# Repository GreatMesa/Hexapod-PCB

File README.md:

# Hexapod-PCB
### 4-Layer PCB for the Arduino Hexapod

## Introduction
This PCB is a 4-Layer hexapod for servo applications. It containes a signal layer for all the servo pwm pins and a uniform ground + power plane for the servos spesifically. The reason while I decided to go through this project is because I wanted a way that I can adjust the voltage level of the servos as depending on the voltage of the servos the speed and tourque is affected. This also will organize my wire managment by a lot since I don't have to extrapolate my electonics to a bunch of breadboards.

## Goals
Here are the main goals of this PCB:
- Make a PCB that can manage 18 seperate servos simutaneously.
- Have uniform and stable power for all 18 servos.
- Make calculations using a inertial sensor for inverse kinematics.
- Use NRF protocol to communicate with a RC transmitter.
- Have indication for the hexapod status using LEDs and a Buzzer.
## PCB 3D Model

## PCB Picture

## Bill of Materials
| Item Name                | Price (USD) | Quantity | Total Price (USD) | Purchase Link                                                                                                                                                                                                                                                                                                                                                                                                                                                                                                                                                                                                                                                                                 |
|--------------------------|-------------|----------|--------------------|----------------------------------------------------------------------------------------------------------------------------------------------------------------------------------------------------------------------------------------------------------------------------------------------------------------------------------------------------------------------------------------------------------------------------------------------------------------------------------------------------------------------------------------------------------------------------------------------------------------------------------------------------------------------------------------------|
| PCB Order               | $33.15      | 1        | $33.15             | [Link](https://www.pcbway.com/QuickOrderOnline.aspx)                                                                                                                                                                                                                                                                                                                                                                                                                                                                                                                                                                                                                                            |
| Teensy 4.1              | $37.50      | 1        | $37.50             | [Link](https://www.amazon.com/PJRC-Cortex-M7-Processor-iMXRT1062-Without/dp/B088JY7P2H)                                                                                                                                                                                                                                                                                                                                                                                                                                                                                                                                                                                                         |
| Male Pin Header Strips  | OWNED       | OWNED    | OWNED              | [Link](https://www.amazon.com/Straight-Breakaway-Connector-Breadboard-Electronic/dp/B09MYBRW3F)                                                                                                                                                                                                                                                                                                                                                                                                                                                                                                                                                                                                |
| Female Pin Header Strips| $0.99       | 1        | $0.99              | [Link](https://www.aliexpress.us/item/2251832850099221.html)                                                                                                                                                                                                                                                                                                                                                                                                                                                                                                                                                                                                                                   |
| 7.4 5200mAh Lipo        | $15.97      | 1        | $15.97             | [Link](https://www.amazon.com/Zeee-5200mAh-Battery-Truggy-Airplane/dp/B06ZYRCPS3)                                                                                                                                                                                                                                                                                                                                                                                                                                                                                                                                                                                                               |
| ACS712 Current Sensor   | $1.15       | 1        | $1.15              | [Link](https://lcsc.com/product-detail/Current-Sensors_ALLEGRO-ACS712ELCTR-05B-T_C44471.html)                                                                                                                                                                                                                                                                                                                                                                                                                                                                                                                                                                                                  |
| WS2812B Individual LEDs | $0.41       | 1        | $0.41              | [Link](https://lcsc.com/product-detail/RGB-LEDs-Built-in-IC_XINGLIGHT-XL-5050RGBC-WS2812B_C2843785.html)                                                                                                                                                                                                                                                                                                                                                                                                                                                                                                                                                                                       |
| SN74HCT125D             | $1.06       | 1        | $1.06              | [Link](https://lcsc.com/product-detail/Buffers-Drivers-Receivers-Transceivers_TI-SN74HCT125DR_C352957.html)                                                                                                                                                                                                                                                                                                                                                                                                                                                                                                                                                                                    |
| 10pc Buzzers            | $0.49       | 1        | $0.49              | [Link](https://lcsc.com/product-detail/Buzzers_YUEXIN-YX-YD2319_C781874.html)                                                                                                                                                                                                                                                                                                                                                                                                                                                                                                                                                                                                                  |
| OLED                    | $1.97       | 1        | $1.97              | [Link](https://lcsc.com/product-detail/OLED-Display_HS-HS96L03W2C03_C5248080.html)                                                                                                                                                                                                                                                                                                                                                                                                                                                                                                                                                                                                              |
| **Total Cost**          |             |          | **$90.72**         |                                                                                                                                                                                                                                                                                                                                                                                                                                                                                                                                                                                                                                                          |

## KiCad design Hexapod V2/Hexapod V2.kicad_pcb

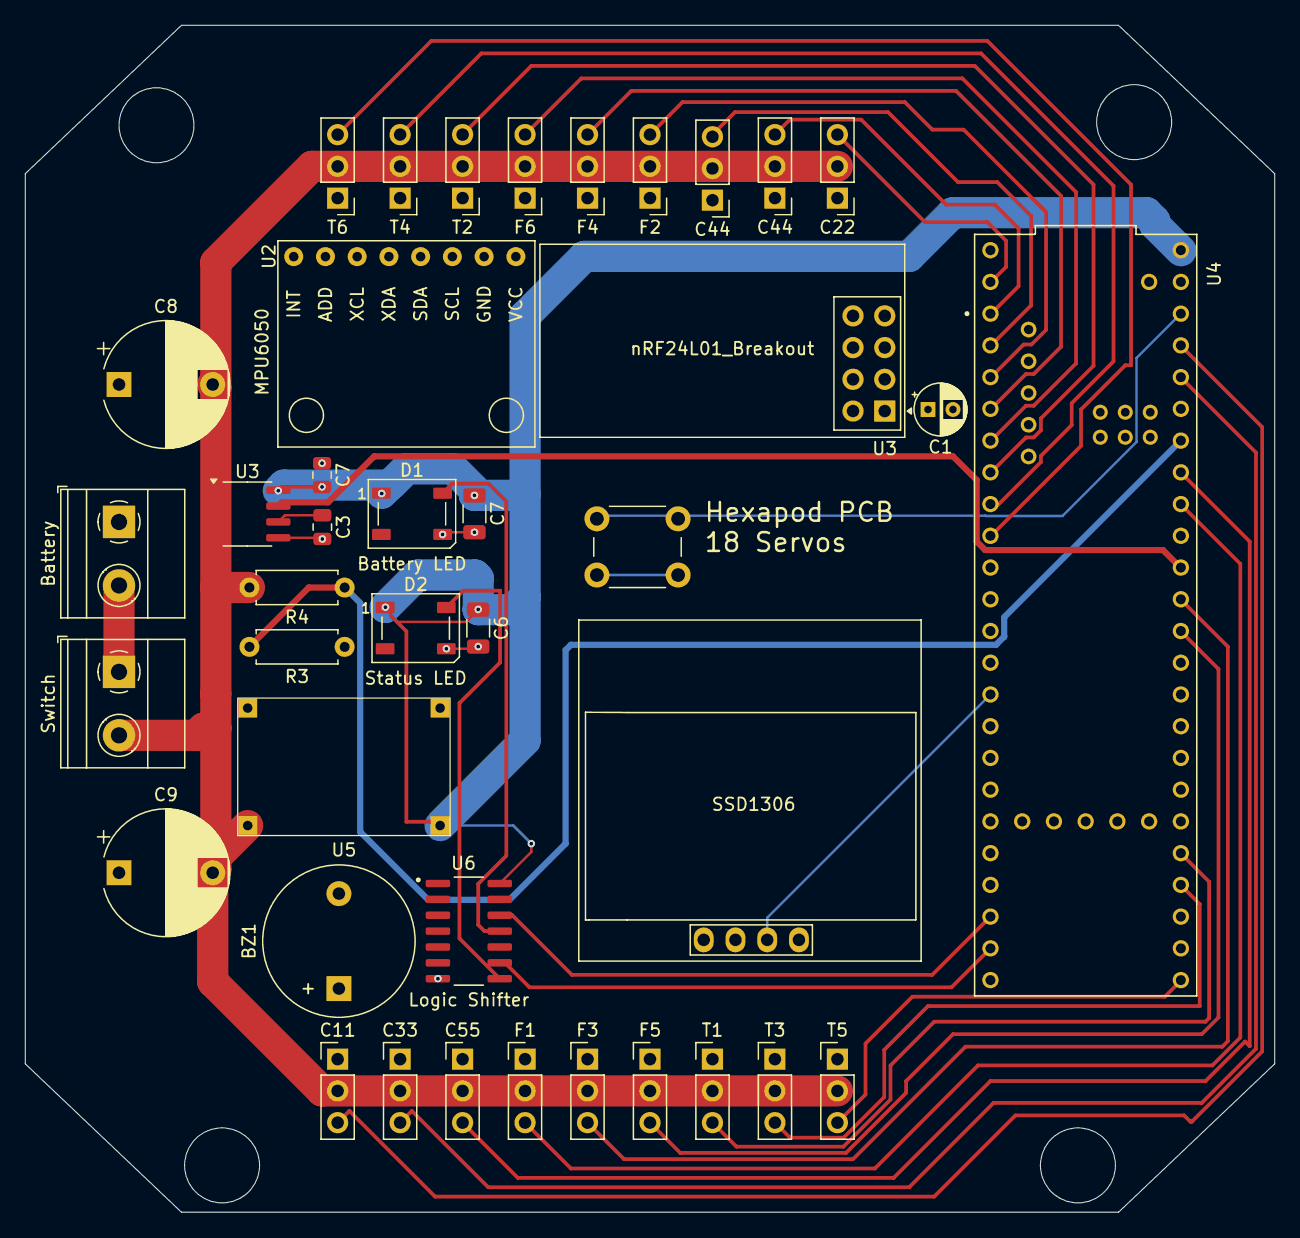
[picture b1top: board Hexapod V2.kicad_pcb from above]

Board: 4 copper layers, 100.0 x 95.0 mm, 39 parts (0 on the bottom side), 36 nets.

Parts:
BZ1: Buzzer; Buzzer_12x9.5RM7.6
C1: 16V 22μF; CP_Radial_D4.0mm_P2.00mm
C3, C7: 102 1nf; C_0805_2012Metric
C6, C7#2: 104 0.1μF; C_1206_3216Metric
C8, C9: 16V 1mF; CP_Radial_D10.0mm_P7.50mm
C11, C22, C33, C44, C44#2, C55: Conn_01x03_Pin; PinHeader_1x03_P2.54mm_Vertical
D1: Battery LED; LED_WS2812B_PLCC4_5.0x5.0mm_P3.2mm
D2: Status LED; LED_WS2812B_PLCC4_5.0x5.0mm_P3.2mm
F1, F2, F3, F4, F5, F6: Conn_01x03_Pin; PinHeader_1x03_P2.54mm_Vertical
J2: Battery; TerminalBlock_Phoenix_MKDS-1,5-2-5.08_1x02_P5.08mm_Horizont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
J3: Switch; TerminalBlock_Phoenix_MKDS-1,5-2-5.08_1x02_P5.08mm_Horizont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
R3, R4: 100kΩ; R_Axial_DIN0207_L6.3mm_D2.5mm_P7.62mm_Horizontal
SSD1306: 128x64OLED
T1, T2, T3, T4, T5, T6: Conn_01x03_Pin; PinHeader_1x03_P2.54mm_Vertical
U2: MPU6050; module_mpu6050
U3: ACS712xLCTR-05B; SOIC-8_3.9x4.9mm_P1.27mm
U3#2: nRF24L01_Breakout
U4: Teensy 4.1; MODULE_DEV-16771
U5: Buck
U6: Logic Shifter; SOIC127P600X175-14N

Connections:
+3.3V: C1.1, SSD1306.2, U2.1 (VCC), U3#2.2, U4.3.3V_1 (3.3V), U4.3.3V_2 (3.3V), U4.3.3V_3 (3.3V)
+5V: C6.1, C7.2, C7#2.1, D1.1 (VDD), D2.1 (VDD), U3.8 (VCC), U4.5V, U4.VIN, U5.2, U6.14
Buzzer: BZ1.1 (+), U4.27 (A13)
CE: U3#2.3, U4.26 (A12)
CSN: U3#2.4, U4.10 (CS1)
Current Reading: U3.7 (VIOUT), U4.16 (A2)
GND: BZ1.2 (-), C1.2, C3.2, C6.2, C7.1, C7#2.2, C8.1, C9.1, C11.1, C22.1, C33.1, C44.1, C44#2.1, C55.1, D1.3 (VSS), D2.3 (VSS), F1.1, F2.1, F3.1, F4.1, F5.1, F6.1, J2.1, R3.1, SSD1306.1, T1.1, T2.1, T3.1, T4.1, T5.1, T6.1, U2.2 (GND), U3.5 (GND), U3#2.1, U4.GND1 (GND), U4.GND2 (GND), U4.GND3 (GND), U4.GND4 (GND), U4.GND5 (GND), U5.1, U5.3, U6.7
LED1: D1.4 (DIN), U4.30 (CRX3), U6.11, U6.12
LED2: D2.4 (DIN), U4.31 (CTX3), U6.8, U6.9
MISO: U3#2.7, U4.12 (MISO)
MOSI: U3#2.6, U4.11 (MOSI)
unnamed: C3.1, U3.6 (FILTER)
unnamed: U4.USB_GND1 (USB_GND), U4.USB_GND2 (USB_GND)
S1: C22.3, U4.0 (RX1)
S2: C44.3, U4.1 (TX1)
S3: C44#2.3, U4.2 (OUT2)
S4: F2.3, U4.3 (LRCLK2)
S5: F4.3, U4.4 (BCLK2)
S6: F6.3, U4.5 (IN2)
S7: T2.3, U4.6 (OUT1D)
S8: T4.3, U4.7 (RX2)
S9: T6.3, U4.8 (TX2)
S10: T5.3, U4.33 (MCLK2)
S11: T3.3, U4.36 (CS2)
S12: T1.3, U4.37 (CS3)
S13: F5.3, U4.14 (A0)
S14: F3.3, U4.15 (A1)
S15: F1.3, U4.18 (A4)
S16: C55.3, U4.19 (A5)
S17: C33.3, U4.22 (A8)
S18: C11.3, U4.23 (A9)
SCK: U3#2.5, U4.13 (SCK)
SCL: U2.3 (SCL), U4.24 (A10)
SDA: U2.4 (SDA), U4.25 (A11)
VD Reading: R3.2, R4.1, U4.20 (A6)
VIN: C8.2, C9.2, C11.2, C22.2, C33.2, C44.2, C44#2.2, C55.2, F1.2, F2.2, F3.2, F4.2, F5.2, F6.2, J2.2, J3.1, J3.2, R4.2, T1.2, T2.2, T3.2, T4.2, T5.2, T6.2, U3.1 (IP+), U3.2 (IP+), U3.3 (IP-), U3.4 (IP-), U5.4

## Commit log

2025-07-11 Submission commit
2025-07-20 Added Teensy
